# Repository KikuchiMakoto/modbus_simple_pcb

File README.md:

# 基板データおよび作成方法置き場

Modbus接続用の簡易基板のデータ置き場です。プロジェクト全体の説明は [modbus_simple_system](https://github.com/KikuchiMakoto/modbus_simple_system) を参照してください。

## 発注先

シンプルな基板なので、[JLCPCB](https://jlcpcb.com/)・[P板.com](https://www.p-ban.com/) など、基板製造を請け負っている業者であればどこでも製造可能です。特定の業者に縛られる必要はありません。

## 組み立て・はんだ付け

基板の組み立てやはんだ付けの手順は [Wiki](https://github.com/KikuchiMakoto/modbus_simple_pcb/wiki) にまとめてあります。基本的にはWikiの内容だけで完結します。

## ガーバーデータ・図面データ

発注に必要なガーバーデータや図面データは [Releaseページ](https://github.com/KikuchiMakoto/modbus_simple_pcb/releases) に置いてあります。

## NDIS/BNC端子・ケース加工

基板本体以外のNDIS/BNC端子の取り付けやケース加工は、出入りの業者に依頼すれば対応してもらえます。

## ライセンス

本リポジトリの回路図・PCB レイアウト・フットプリント・シンボル等の**ハードウェア設計ファイル**は
**CERN Open Hardware Licence Version 2 — Strongly Reciprocal (CERN-OHL-S 2.0)** の下で公開しています。
詳細はリポジトリ同梱の [`LICENSE-CERN-OHL-S-2.0.txt`](./LICENSE-CERN-OHL-S-2.0.txt) を参照してください。

- SPDX: `CERN-OHL-S-2.0`
- 派生物は同じライセンスでの配布が必要です（strong copyleft）。
- KiCad のプロジェクトファイル、Gerber、回路図シンボル／フットプリントが対象です。

ファームウェア ([modbus_simple_firmware](https://github.com/KikuchiMakoto/modbus_simple_firmware)) は MIT、
ドキュメント ([modbus_simple_system](https://github.com/KikuchiMakoto/modbus_simple_system)) も MIT です。
リポジトリごとにライセンスが異なるため、混在させる場合はそれぞれの LICENSE を確認してください。

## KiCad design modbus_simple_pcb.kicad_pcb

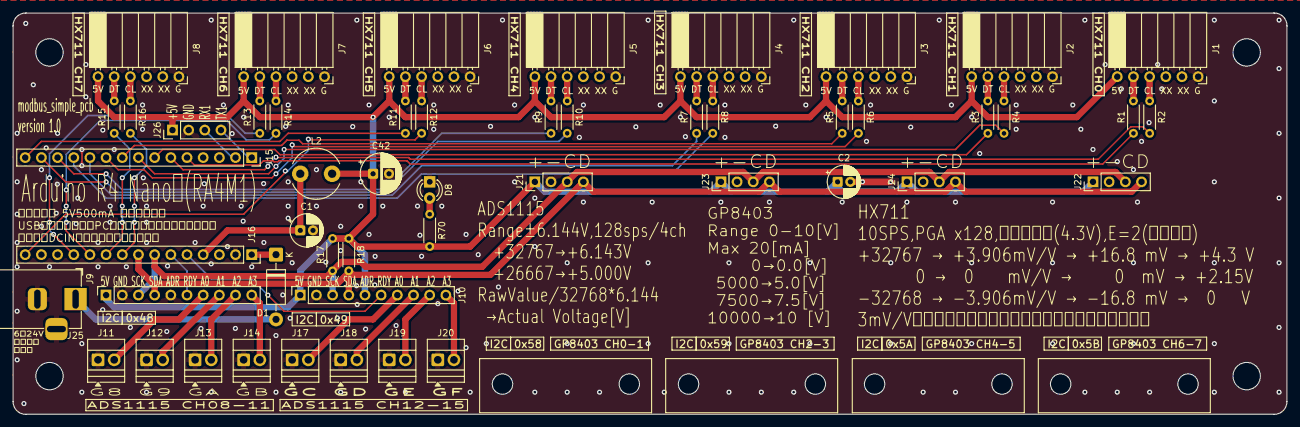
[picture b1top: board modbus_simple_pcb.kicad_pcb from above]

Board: 2 copper layers, 200.0 x 63.0 mm, 51 parts (0 on the bottom side), 52 nets.

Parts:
C1, C2: 10μF50V; CP_Radial_D5.0mm_P2.00mm
C42: 220μF16V; CP_Radial_D6.3mm_P2.50mm
D1: SBM245L; D_DO-41_SOD81_P10.16mm_Horizontal
D8: OSR5JA3Z74A; LED_D3.0mm
J1, J2, J3, J4, J5, J6, J7, J8: L_PinSocket; Akitsuki_HX711_Socket_1x06_P2.54mm_Horizontal
J9, J10: ADS1115; PinSocket_1x10_P2.54mm_Vertical
J11, J12, J13, J14, J17, J18, J19, J20: Screw_Terminal_01x02; TerminalBlock_Xinya_XY308-2.54-2P_1x02_P2.54mm_Horizontal
J15, J16: KH-2.54FH-1X15P-H8.5; PinSocket_1x15_P2.54mm_Vertical
J21, J22, J23, J24, J26: GP8403; PinHeader_1x04_P2.54mm_Vertical
J25: MJ-179PH; BarrelJack_Horizontal
L2: 100μH1.5A; L_Radial_D7.8mm_P5.00mm_Fastron_07HCP
R1, R2, R3, R4, R5, R6, R7, R8, R9, R10, R11, R12, R13, R14, R15, R16: 100; R_Axial_DIN0204_L3.6mm_D1.6mm_P5.08mm_Horizontal
R17, R18, R70: 3.3k; R_Axial_DIN0204_L3.6mm_D1.6mm_P5.08mm_Horizontal

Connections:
+5V: C2.1, C42.1, J1.1, J2.1, J3.1, J4.1, J5.1, J6.1, J7.1, J8.1, J9.1, J10.1, J10.5, J21.1, J22.1, J23.1, J24.1, J26.1, L2.2, R17.2, R18.2, R70.2
ADS1115_0_A0: J9.7, J11.2
ADS1115_0_A1: J9.8, J12.2
ADS1115_0_A2: J9.9, J13.2
ADS1115_0_A3: J9.10, J14.2
ADS1115_0_RDY: J9.6, J16.6
ADS1115_1_A0: J10.7, J17.2
ADS1115_1_A1: J10.8, J18.2
ADS1115_1_A2: J10.9, J19.2
ADS1115_1_A3: J10.10, J20.2
ADS1115_1_RDY: J10.6, J16.5
GND: C1.2, C2.2, C42.2, D8.1 (K), J1.6, J2.6, J3.6, J4.6, J5.6, J6.6, J7.6, J8.6, J9.2, J9.5, J10.2, J11.1, J12.1, J13.1, J14.1, J15.4, J16.2, J17.1, J18.1, J19.1, J20.1, J21.2, J22.2, J23.2, J24.2, J25.2, J25.3, J26.2
HX711_0_DOUT: J15.5, R1.1
HX711_0_SCK: J15.6, R2.1
HX711_1_DOUT: J15.7, R3.1
HX711_1_SCK: J15.8, R4.1
HX711_2_DOUT: J15.9, R5.1
HX711_2_SCK: J15.10, R6.1
HX711_3_DOUT: J15.11, R7.1
HX711_3_SCK: J15.12, R8.1
HX711_4_DOUT: J15.13, R9.1
HX711_4_SCK: J15.14, R10.1
HX711_5_DOUT: J15.15, R11.1
HX711_5_SCK: J16.15, R12.1
HX711_6_DOUT: J16.12, R13.1
HX711_6_SCK: J16.11, R14.1
HX711_7_DOUT: J16.10, R15.1
HX711_7_SCK: J16.9, R16.1
I2C_SCK: J9.3, J10.3, J16.7, J21.3, J22.3, J23.3, J24.3, R17.1
I2C_SDA: J9.4, J10.4, J16.8, J21.4, J22.4, J23.4, J24.4, R18.1
unnamed: D1.2 (A), J25.1
unnamed: D8.2 (A), R70.1
unnamed: J1.2, R1.2
unnamed: J1.3, R2.2
unnamed: J2.2, R3.2
unnamed: J2.3, R4.2
unnamed: J3.2, R5.2
unnamed: J3.3, R6.2
unnamed: J4.2, R7.2
unnamed: J4.3, R8.2
unnamed: J5.2, R9.2
unnamed: J5.3, R10.2
unnamed: J6.2, R11.2
unnamed: J6.3, R12.2
unnamed: J7.2, R13.2
unnamed: J7.3, R14.2
unnamed: J8.2, R15.2
unnamed: J8.3, R16.2
unnamed: C1.1, J16.4, L2.1
UART1_RX_PIN: J15.2, J26.3
UART1_TX_PIN: J15.1, J26.4
VIN: D1.1 (K), J16.1

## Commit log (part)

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2026-05-11 add .gitignore for KiCad PCB project
2026-05-11 Add new symbol library configuration for New_Library
    - Created a new symbol library table entry for "New_Library"
    - Set library type to "KiCad" with appropriate URI and description
2026-05-11 Refactor polygon coordinates for improved accuracy in PCB layout
2026-05-12 Add funding configuration in FUNDING.yml
2026-05-19 update all resource
